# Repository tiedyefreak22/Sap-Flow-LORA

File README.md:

# packet-forwarder

This firmware project was created using [Particle Developer Tools](https://www.particle.io/developer-tools/) and is compatible with all [Particle Devices](https://www.particle.io/devices/).

Feel free to replace this README.md file with your own content, or keep it for reference.

## Table of Contents
- [Introduction](#introduction)
- [Prerequisites To Use This Template](#prerequisites-to-use-this-repository)
- [Getting Started](#getting-started)
- [Particle Firmware At A Glance](#particle-firmware-at-a-glance)
  - [Logging](#logging)
  - [Setup and Loop](#setup-and-loop)
  - [Delays and Timing](#delays-and-timing)
  - [Testing and Debugging](#testing-and-debugging)
  - [GitHub Actions (CI/CD)](#github-actions-cicd)
  - [OTA](#ota)
- [Support and Feedback](#support-and-feedback)
- [Version](#version)

## Introduction

For an in-depth understanding of this project template, please refer to our [documentation](https://docs.particle.io/firmware/best-practices/firmware-template/).

## Prerequisites To Use This Repository

To use this software/firmware on a device, you'll need:

- A [Particle Device](https://www.particle.io/devices/).
- Windows/Mac/Linux for building the software and flashing it to a device.
- [Particle Development Tools](https://docs.particle.io/getting-started/developer-tools/developer-tools/) installed and set up on your computer.
- Optionally, a nice cup of tea (and perhaps a biscuit).

## Getting Started

1. While not essential, we recommend running the [device setup process](https://setup.particle.io/) on your Particle device first. This ensures your device's firmware is up-to-date and you have a solid baseline to start from.

2. If you haven't already, open this project in Visual Studio Code (File -> Open Folder). Then [compile and flash](https://docs.particle.io/getting-started/developer-tools/workbench/#cloud-build-and-flash) your device. Ensure your device's USB port is connected to your computer.

3. Verify the device's operation by monitoring its logging output:
    - In Visual Studio Code with the Particle Plugin, open the [command palette](https://docs.particle.io/getting-started/developer-tools/workbench/#particle-commands) and choose "Particle: Serial Monitor".
    - Or, using the Particle CLI, execute:
    ```
    particle serial monitor --follow
    ```

4. Uncomment the code at the bottom of the cpp file in your src directory to publish to the Particle Cloud! Login to console.particle.io to view your devices events in real time.

5. Customize this project! For firmware details, see [Particle firmware](https://docs.particle.io/reference/device-os/api/introduction/getting-started/). For information on the project's directory structure, visit [this link](https://docs.particle.io/firmware/best-practices/firmware-template/#project-overview).

## Particle Firmware At A Glance

### Logging

The firmware includes a [logging library](https://docs.particle.io/reference/device-os/api/logging/logger-class/). You can display messages at different levels and filter them:

```
Log.trace("This is trace message");
Log.info("This is info message");
Log.warn("This is warn message");
Log.error("This is error message");
```

### Setup and Loop

Particle projects originate from the Wiring/Processing framework, which is based on C++. Typically, one-time setup functions are placed in `setup()`, and the main application runs from the `loop()` function.

For advanced scenarios, explore our [threading support](https://docs.particle.io/firmware/software-design/threading-explainer/).

### Delays and Timing

By default, the setup() and loop() functions are blocking whilst they run, meaning that if you put in a delay, your entire application will wait for that delay to finish before anything else can run. 

For techniques that allow you to run multiple tasks in parallel without creating threads, checkout the code example [here](https://docs.particle.io/firmware/best-practices/firmware-template/).

(Note: Although using `delay()` isn't recommended for best practices, it's acceptable for testing.)

### Testing and Debugging

For firmware testing and debugging guidance, check [this documentation](https://docs.particle.io/troubleshooting/guides/build-tools-troubleshooting/debugging-firmware-builds/).

### GitHub Actions (CI/CD)

This project provides a YAML file for GitHub, automating firmware compilation whenever changes are pushed. More details on [Particle GitHub Actions](https://docs.particle.io/firmware/best-practices/github-actions/) are available.

### OTA

To learn how to utilize Particle's OTA service for device updates, consult [this documentation](https://docs.particle.io/getting-started/cloud/ota-updates/).

Test OTA with the 'Particle: Cloud Flash' command in Visual Studio Code or the CLI command 'particle flash'!

This firmware supports binary assets in OTA packages, allowing the inclusion of audio, images, configurations, and external microcontroller firmware. More details are [here](https://docs.particle.io/reference/device-os/api/asset-ota/asset-ota/).

## Support and Feedback

For support or feedback on this template or any Particle products, please join our [community](https://community.particle.io)!

## Version

Template version 1.0.2

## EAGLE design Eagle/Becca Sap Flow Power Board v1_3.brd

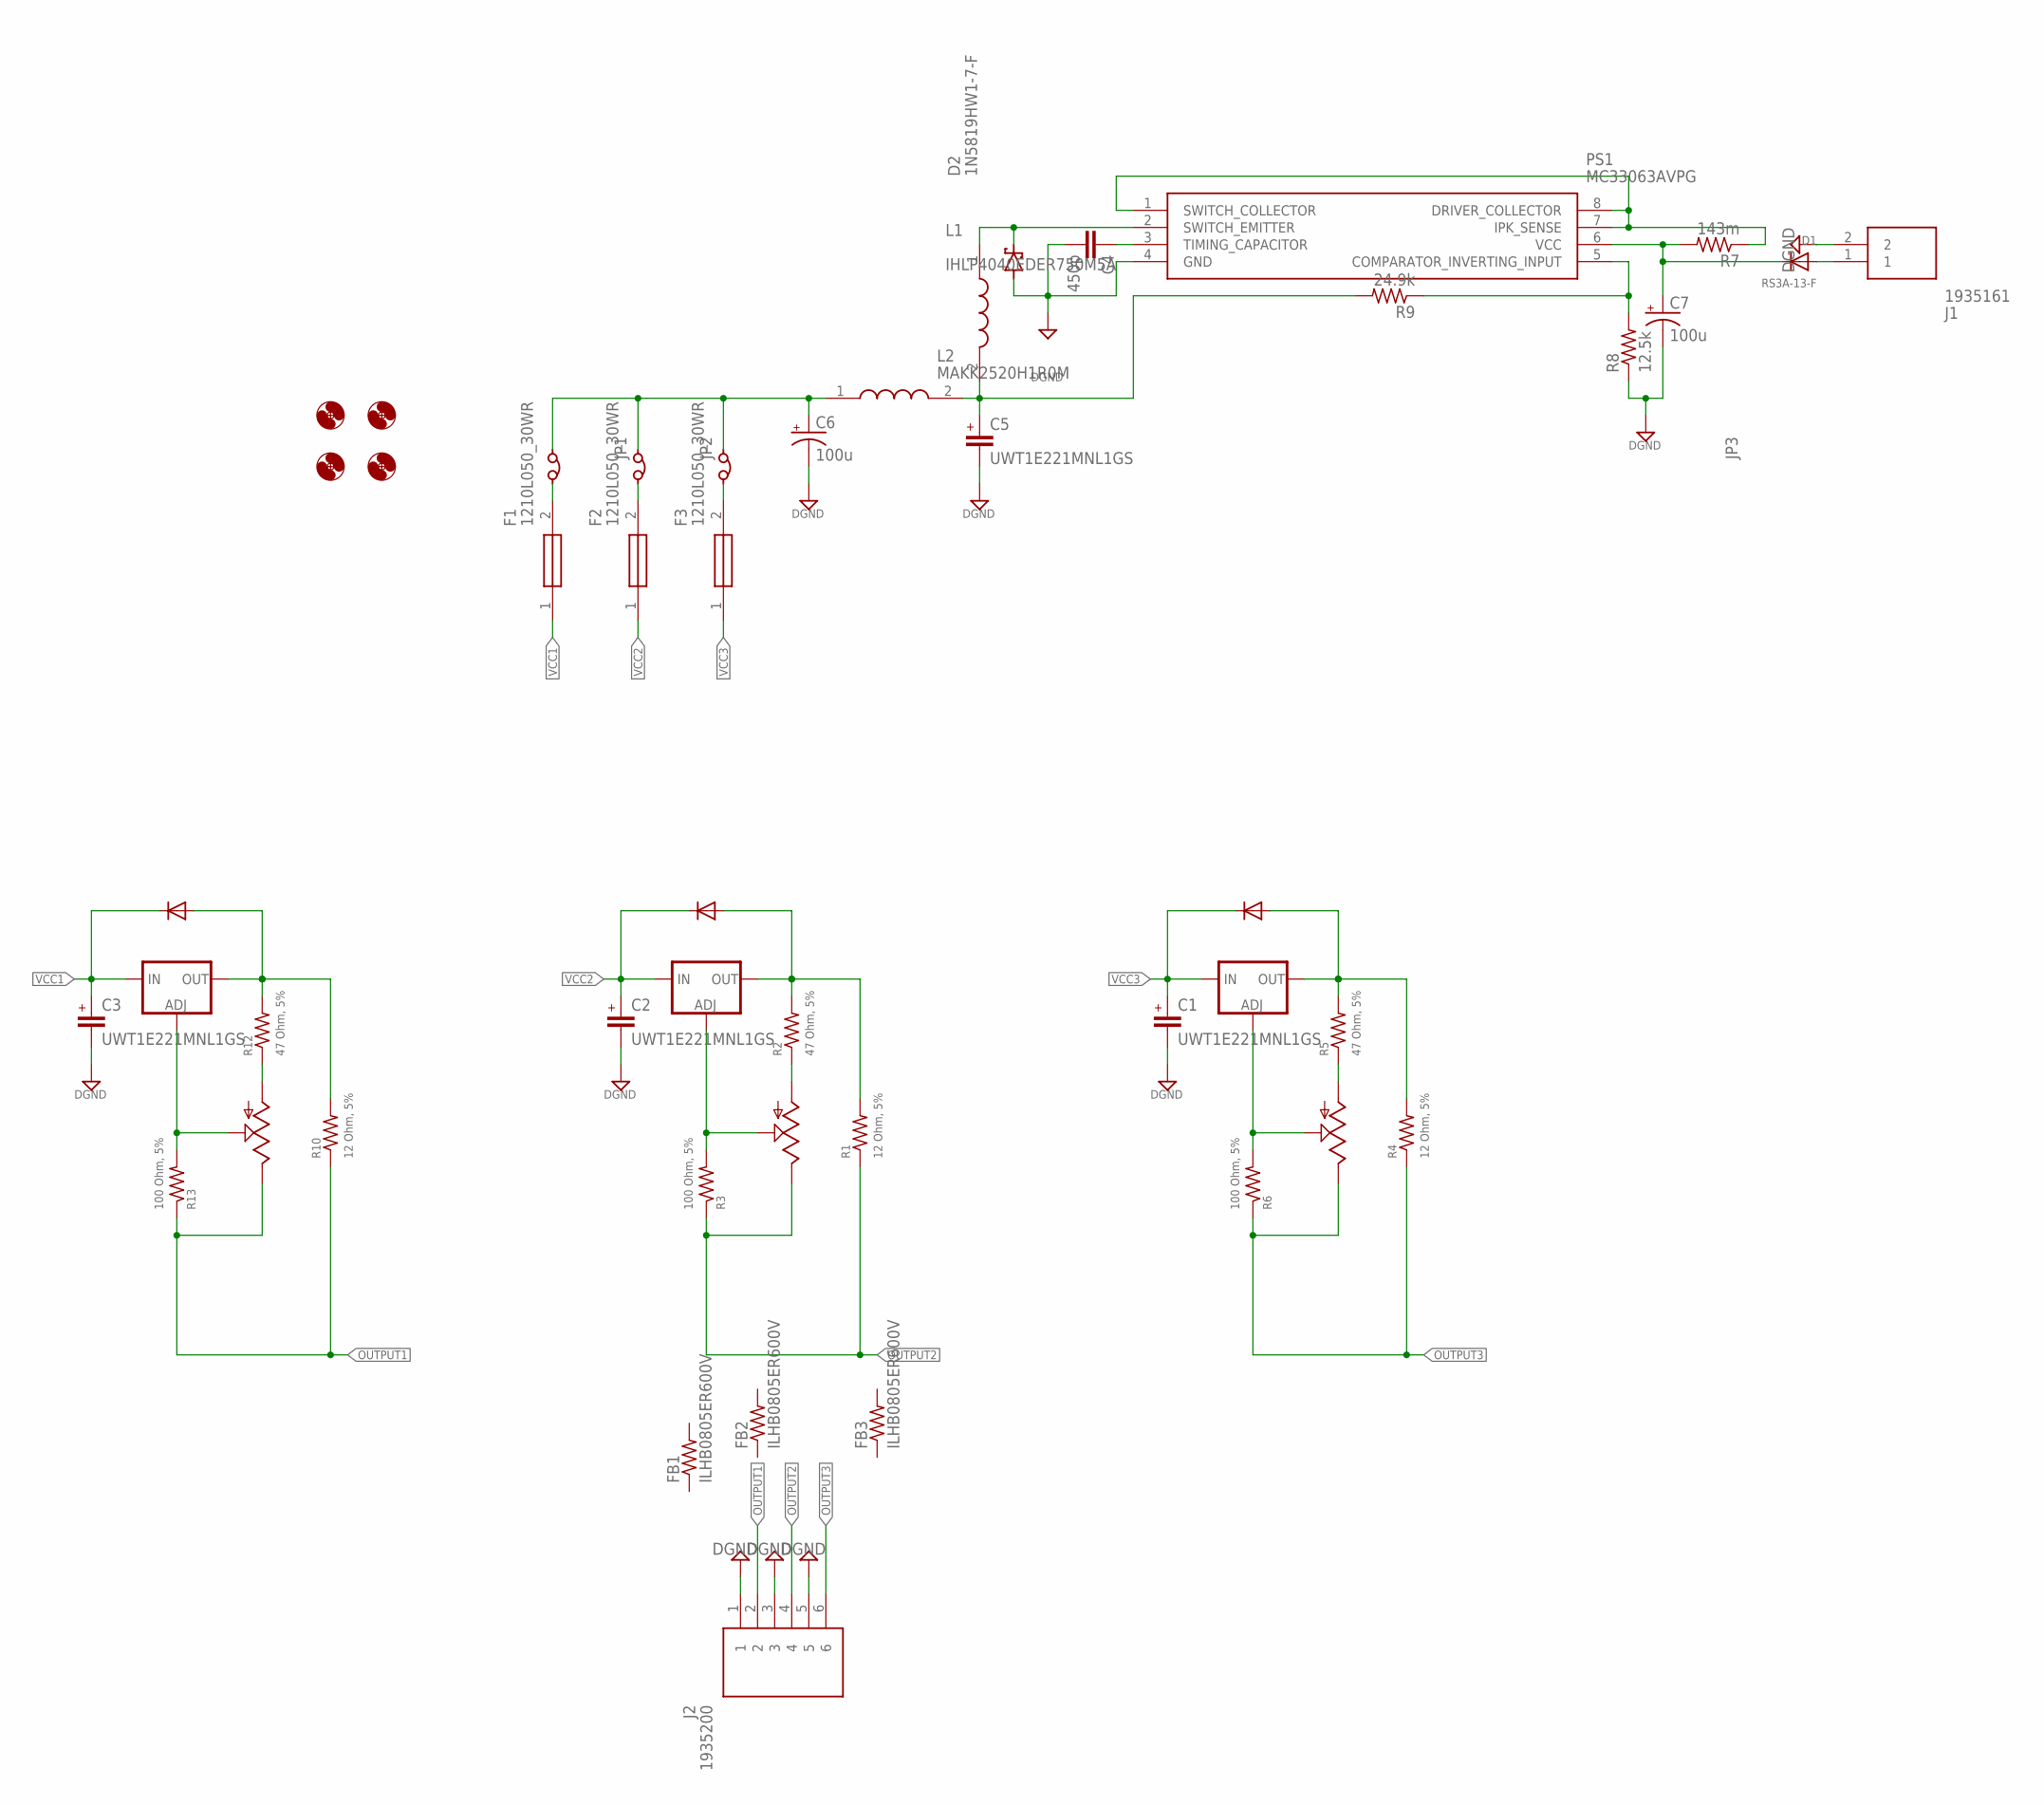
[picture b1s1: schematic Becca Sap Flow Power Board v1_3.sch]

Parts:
C1, C2, C3, C5: UWT1E221MNL1GS; CAPAE830X1080N
C4: 450p; C0603
C6, C7: 100u; E2,5-6
D1: RS3A-13-F; DIOM7959X250N
D2: 1N5819HW1-7-F; SODFL3518X115N
D3, D4, D6: S1A; DIOM5027X250N
F1, F2, F3: 1210L050_30WR; THRMC3226X125N
FB1, FB2, FB3: ILHB0805ER600V; BEADC2012X110N
J1: 1935161
J2: 1935200
JP1, JP2, JP3: JUMPER; HDR2X1
L1: IHLP4040EDER750M5A; INDPM115103X540N
L2: MAKK2520H1R0M
PS1: MC33063AVPG; DIP794W56P254L959H533Q8N
R1, R4, R10: 12 Ohm, 5%; R1210
R2, R5, R12: 47 Ohm, 5%; R1210
R3, R6, R13: 100 Ohm, 5%; R1210
R7: 143m; R0603
R8: 12.5k; R0603
R9: 24.9k; R0603
U1, U2, U3: LM317MBSTT3G; SOT230P700X175-4N
U$1, U$2, U$3, U$4: MOUNT-HOLE3.0; 3,0
VR1, VR2, VR3: 3296W-1-102RLF; 3296W1102RLF

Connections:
DGND: C1.2, C2.2, C3.2, C4.2, C5.2, C6.-, C7.-, D2.2 (A), J1.2, J2.1, J2.3, J2.5, PS1.4 (GND), R8.1
unnamed: C6.+, JP1.1, JP2.1, JP3.1, L2.1
unnamed: D3.2 (A), R1.2, R2.2, U2.2 (OUT)
unnamed: F1.2, JP3.2
unnamed: F2.2, JP1.2
unnamed: D1.2 (A), J1.1
unnamed: PS1.1 (SWITCH_COLLECTOR), PS1.7 (IPK_SENSE), PS1.8 (DRIVER_COLLECTOR), R7.1
unnamed: R3.2, U2.1 (ADJ), VR2.2 (S)
unnamed: F3.2, JP2.2
unnamed: C7.+, D1.1 (K), PS1.6 (VCC), R7.2
unnamed: R2.1, VR2.1 (A)
unnamed: D4.2 (A), R4.2, R5.2, U3.2 (OUT)
unnamed: D6.2 (A), R10.2, R12.2, U1.2 (OUT)
unnamed: R6.2, U3.1 (ADJ), VR3.2 (S)
unnamed: R13.2, U1.1 (ADJ), VR1.2 (S)
unnamed: R12.1, VR1.1 (A)
unnamed: R5.1, VR3.1 (A)
unnamed: C4.1, PS1.3 (TIMING_CAPACITOR)
unnamed: PS1.5 (COMPARATOR_INVERTING_INPUT), R8.2, R9.1
unnamed: D2.1 (C), L1.1, PS1.2 (SWITCH_EMITTER)
unnamed: C5.1, L1.2, L2.2, R9.2
OUTPUT1: J2.2, R10.1, R13.1, VR1.3 (E)
OUTPUT2: J2.4, R1.1, R3.1, VR2.3 (E)
OUTPUT3: J2.6, R4.1, R6.1, VR3.3 (E)
VCC1: C3.1, D6.1 (K), F1.1, U1.3 (IN)
VCC2: C2.1, D3.1 (K), F2.1, U2.3 (IN)
VCC3: C1.1, D4.1 (K), F3.1, U3.3 (IN)

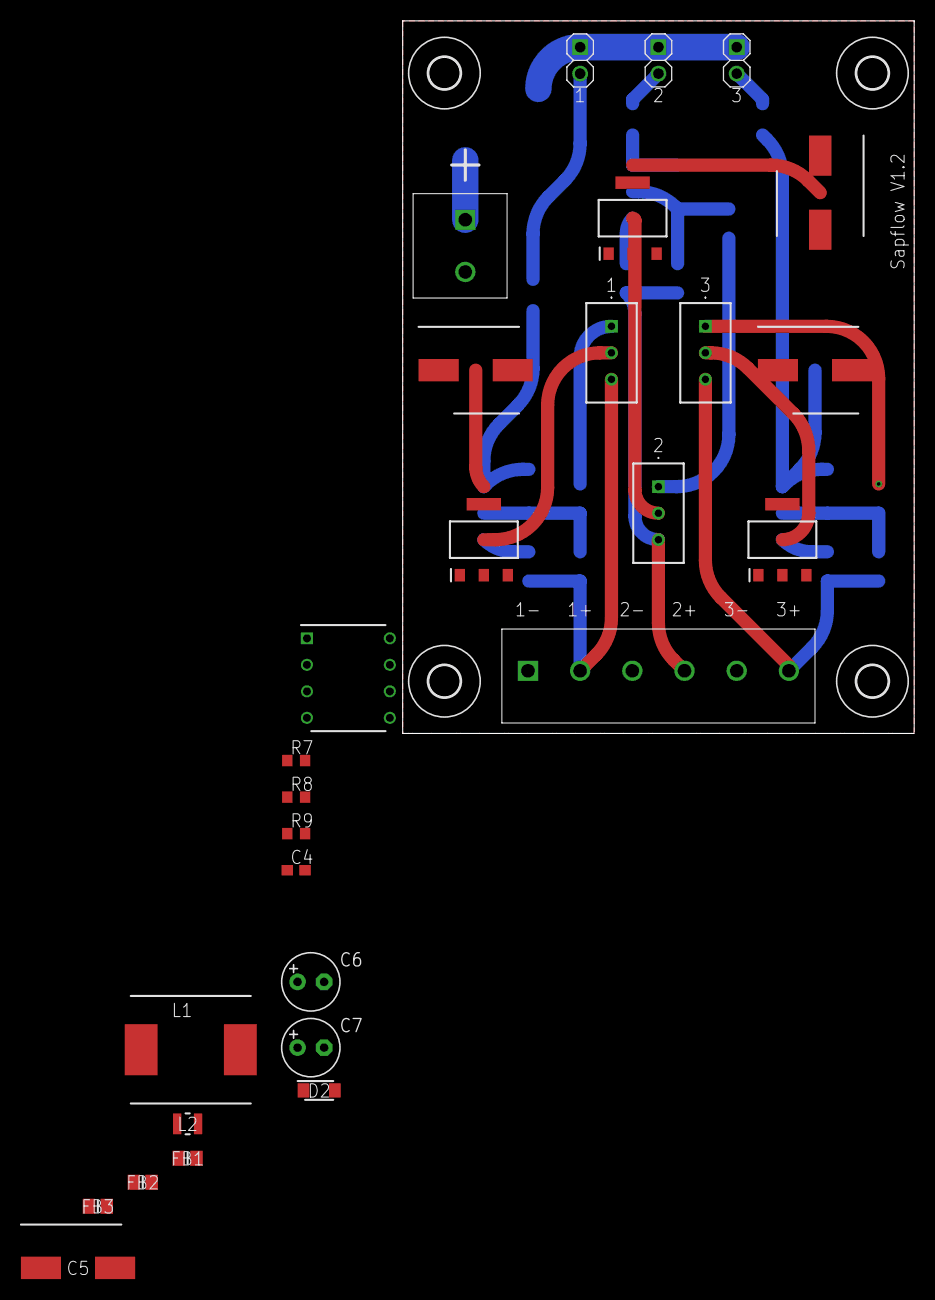
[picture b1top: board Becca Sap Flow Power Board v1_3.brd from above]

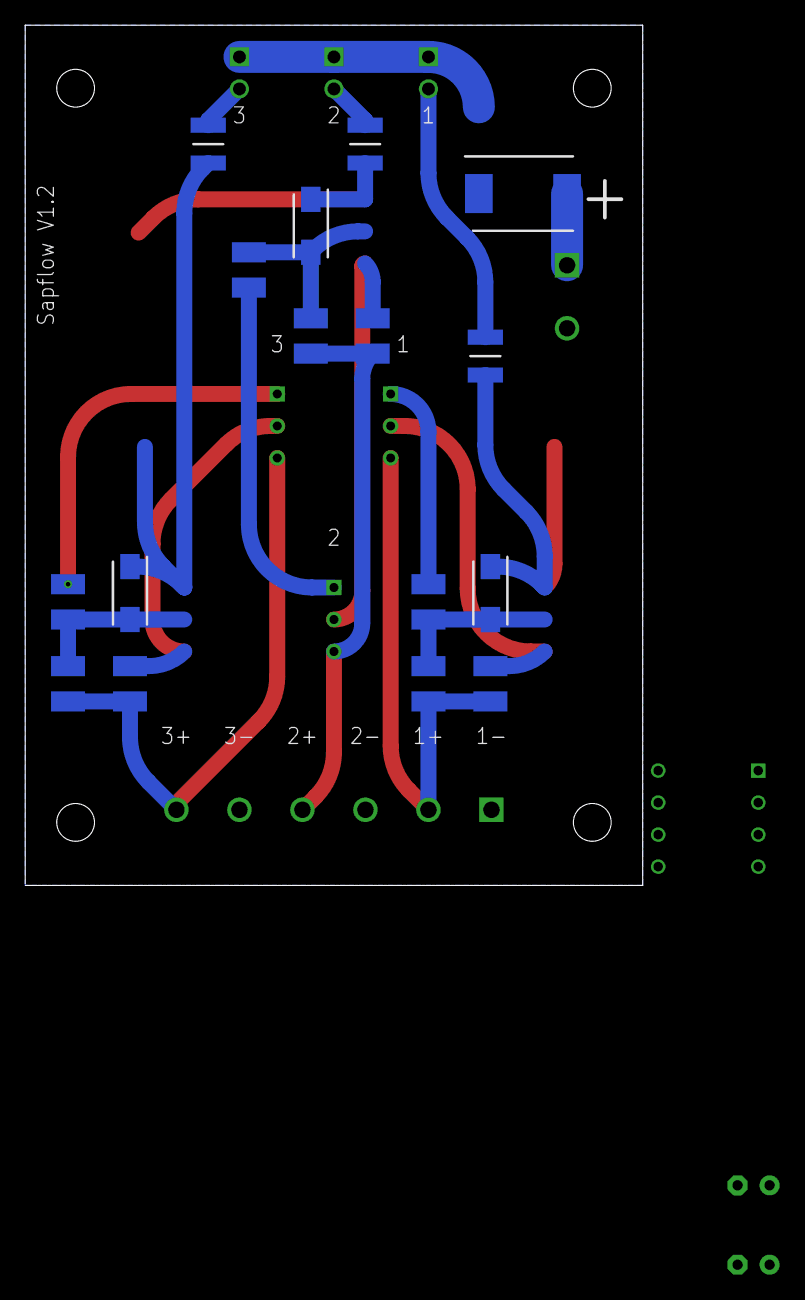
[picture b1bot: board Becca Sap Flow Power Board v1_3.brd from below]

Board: 2 copper layers, 49.0 x 68.3 mm, 48 parts (16 on the bottom side), 27 nets.

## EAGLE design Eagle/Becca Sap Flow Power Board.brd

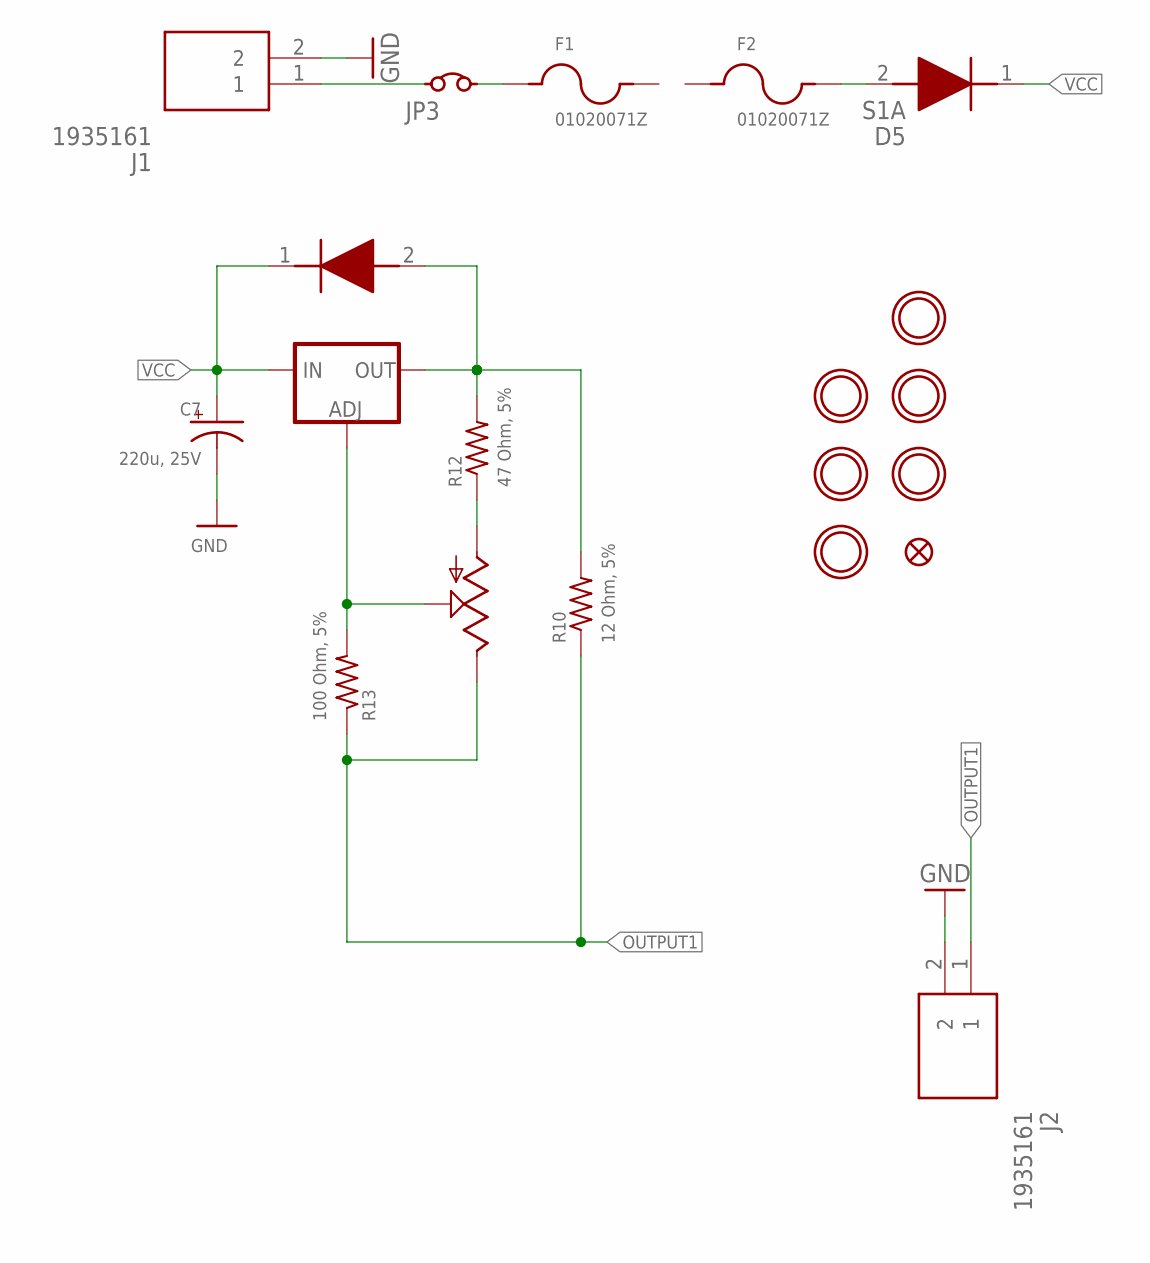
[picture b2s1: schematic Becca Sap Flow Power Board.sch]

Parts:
C7: 220u, 25V; PANASONIC_C
D5, D6: S1A; DIOM5027X250N
F1, F2: 01020071Z
FID2: FIDUCIAL_1MM
J1, J2: 1935161
JP3: JUMPER; HDR2X1
R10: 12 Ohm, 5%; R0805
R12: 47 Ohm, 5%; R0805
R13: 100 Ohm, 5%; R0805
U1: V_REG_317SMD; SOT223
U$1, U$2, U$3, U$4, U$5, U$11: MOUNTINGHOLE2.5; MOUNTINGHOLE_2.5_PLATED
VR1: 3296W-1-102RLF; 3296W1102RLF

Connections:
GND: C7.-, J1.2, J2.2
unnamed: J1.1, JP3.1
unnamed: F1.1, JP3.2
unnamed: D5.2 (A), F2.2
unnamed: D6.2 (A), R10.2, R12.2, U1.2 (OUT)
unnamed: R13.2, U1.1 (ADJ), VR1.2 (S)
unnamed: R12.1, VR1.1 (A)
OUTPUT1: J2.1, R10.1, R13.1, VR1.3 (E)
VCC: C7.+, D5.1 (K), D6.1 (K), U1.3 (IN)

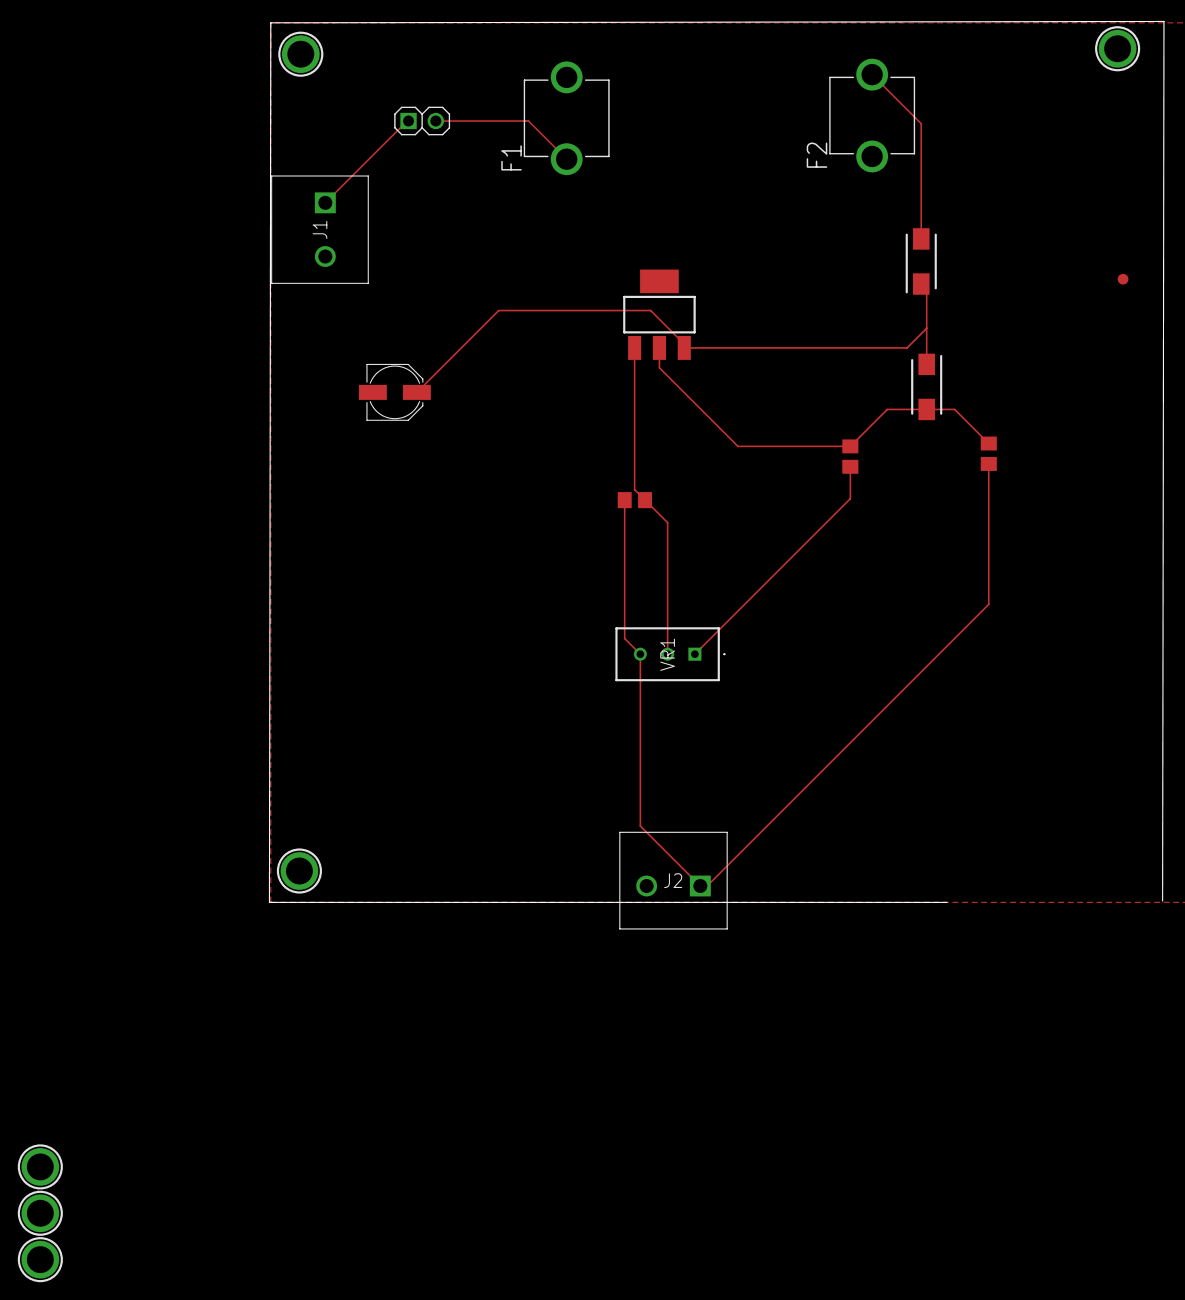
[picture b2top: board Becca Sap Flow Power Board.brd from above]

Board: 2 copper layers, 83.3 x 82.0 mm, 20 parts (0 on the bottom side), 9 nets.

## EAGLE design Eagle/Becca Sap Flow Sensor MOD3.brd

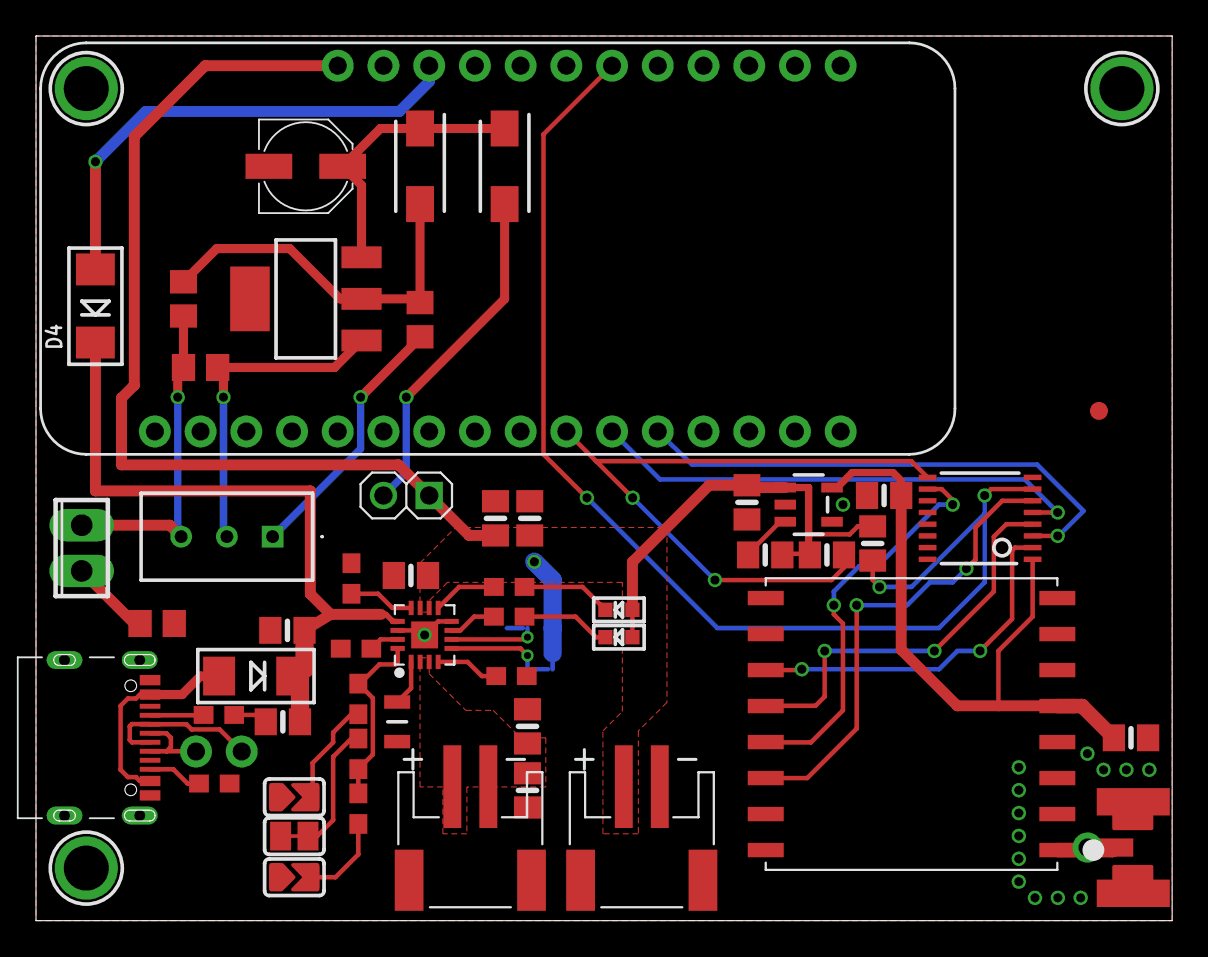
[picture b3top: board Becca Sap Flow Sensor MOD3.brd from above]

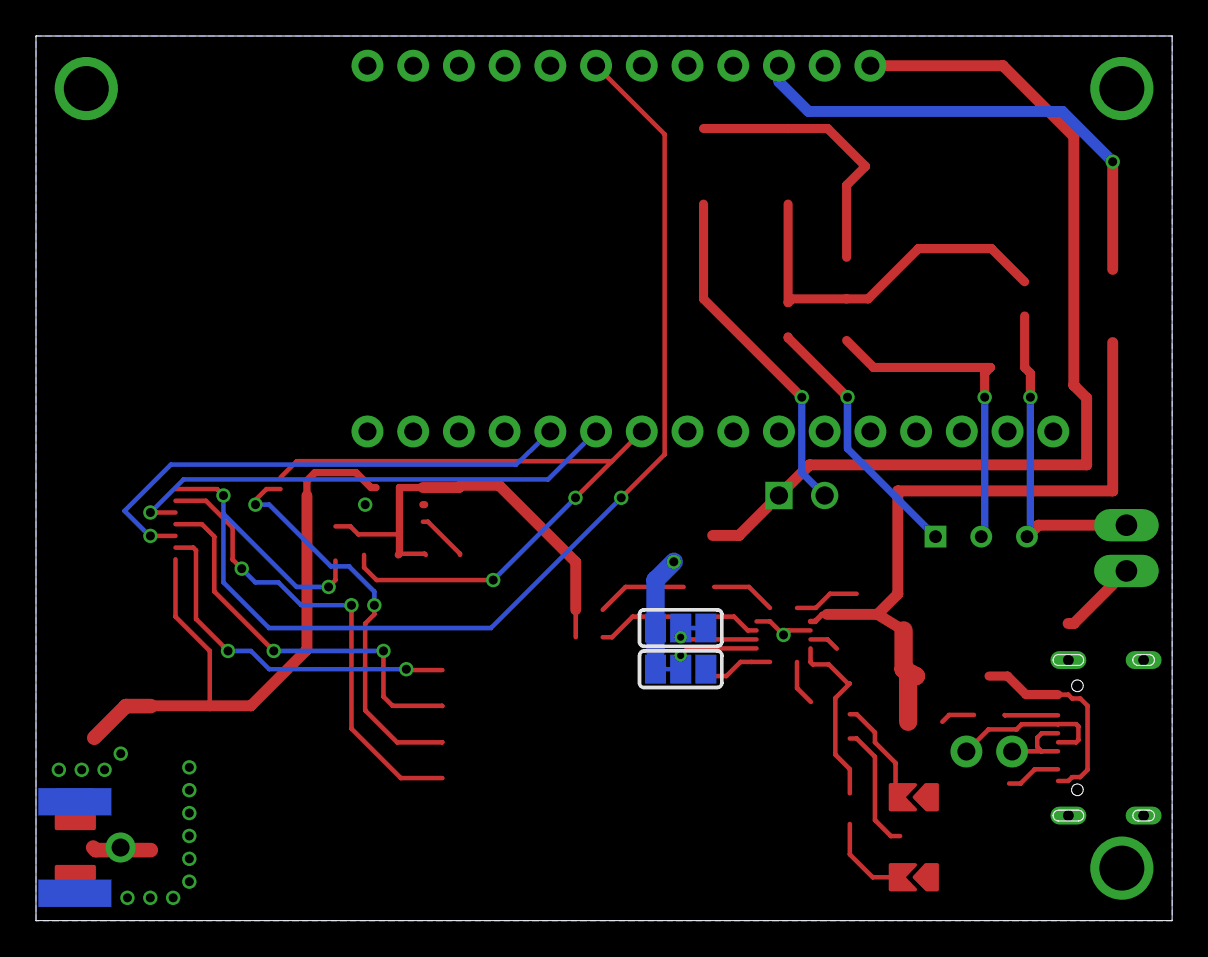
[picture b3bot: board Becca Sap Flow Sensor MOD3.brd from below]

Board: 2 copper layers, 63.1 x 49.1 mm, 59 parts (2 on the bottom side), 42 nets.

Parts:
0.5A, 1.5A: SOLDERJUMPER_ARROW_NOPASTE
1A: SOLDERJUMPER_CLOSEDWIRE
BATT: JST 2PH; JST-PH-2-SMT-RA
C1, C2, C3, C4, C5, C6, C9, C10, C14: 10uF; 0805-NO
C7: 220u, 25V; PANASONIC_C
C8: 0.1uF; 0805-NO
D1: GREEN; CHIPLED_0603
D2, D4: SK34A; SMADIODE
D3: RED; CHIPLED_0603
D5, D6: S1A; DIOM5027X250N
FID2: FIDUCIAL_1MM
JP1: 1X02_ROUND
JP3: JUMPER; HDR2X1
JP7: 1X01_ROUND
R1, R9: 1K; 0603-NO
R2, R7, R8, R11: 10K; 0603-NO
R3: 590; 0603-NO
R4, R6: 5.1K; 0603-NO
R5: 2K; 0603-NO
R10: 12 Ohm, 5%; R0805
R12: 47 Ohm, 5%; R0805
R13: 100 Ohm, 5%; R0805
R14: R of 2 Thermos; R0805
R15, R16, R17: 100K; 0805-NO
RT1: NTCS0805E3103FHT; THRMC2012X95N
SJ1, SJ2: SOLDERJUMPER_2WAY_OPEN_NOPASTE
SYSOUT: JST 2PH; JST-PH-2-SMT-RA
U1: V_REG_317SMD; SOT223
U2: BORON
U6: RFM69HCW; RFMHCW_SMT
U7: 74HC4050D; TSSOP16
U8: AP2112K-3.3; SOT23-5
U$3, U$4, U$11: MOUNTINGHOLE2.5; MOUNTINGHOLE_2.5_PLATED
VR1: 3296W-1-102RLF; 3296W1102RLF
X1: 2POL254
X2: USB Type C; USB_C_CUSB31-CFM2AX-01-X
X4: BQ24074; QFN16_3MM
X5: uFL/SMA; SMA_EDGELAUNCH_UFL

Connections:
3.3V: C8.1, C14.1, U6.5P, U7.1, U8.5
!CE: R8.1, X4.4
!CHG: R7.1, X4.9
!PGOOD: R11.1, X4.7
CC1: R6.2, X2.A5
CC2: R4.2, X2.B5
CS_3V1: U6.13P, U7.10
CS_5V1: R16.1, U2.10, U7.9
D+: JP1.1, X2.A6, X2.B6
D-: JP1.2, X2.A7, X2.B7
EN1: SJ2.2, X4.6
EN2: SJ1.2, X4.5
EN3: R15.2, U8.3
GND: 0.5A.1, 1.5A.1, 1A.1, BATT.2, C1.2, C2.2, C3.2, C4.2, C5.2, C6.2, C7.-, C8.2, C9.2, C10.2, C14.2, R1.2, R2.2, R4.1, R6.1, R8.2, R14.1, RT1.2, SJ1.3, SJ2.3, SYSOUT.2, U2.4, U6.2P, U6.9P, U6.16P, U7.8, U8.2, X2.A1B12, X2.B1A12, X4.8, X4.14, X4.THERMAL, X5.GND@1, X5.GND@2, X5.GND@3, X5.GND@4
ILIM: R1.1, X4.12
ISET: R3.1, R5.1, R9.1, X4.16
ITERM: R2.1, X4.15
MOSI_3V1: U6.11P, U7.2
MOSI_5V1: U2.12, U7.3
unnamed: D1.C, R11.2
unnamed: D3.C, R7.2
unnamed: 1.5A.2, R3.2
unnamed: 0.5A.2, R5.2
unnamed: 1A.2, R9.2
unnamed: RT1.1, X4.1
unnamed: D5.2, JP3.2
unnamed: C7.+, D5.1, D6.1, U1.3
unnamed: D6.2, R10.2, R12.2, U1.2
unnamed: R14.2, X1.1
unnamed: R13.2, U1.1, VR1.2
unnamed: R12.1, VR1.1
unnamed: R10.1, R13.1, VR1.3, X1.2
unnamed: JP7.1, U6.1P, X5.P
OUT: C2.1, C3.1, C4.1, C10.1, D1.A, D3.A, JP3.1, R15.1, R16.2, R17.2, SJ1.1, SJ2.1, SYSOUT.1, U2.28, U8.1, X4.10, X4.11
RST_3V1: U6.14P, U7.6
RST_5V1: R17.1, U2.22, U7.7
SCK_3V1: U6.12P, U7.4
SCK_5V1: U2.11, U7.5
VBUS: C1.1, C9.1, D2.C, D4.C, X4.13
VLIPO: BATT.1, C5.1, C6.1, X4.2, X4.3
VUSB: D2.A, X2.A4B9, X2.B4A9
VUSB1: D4.A, U2.26

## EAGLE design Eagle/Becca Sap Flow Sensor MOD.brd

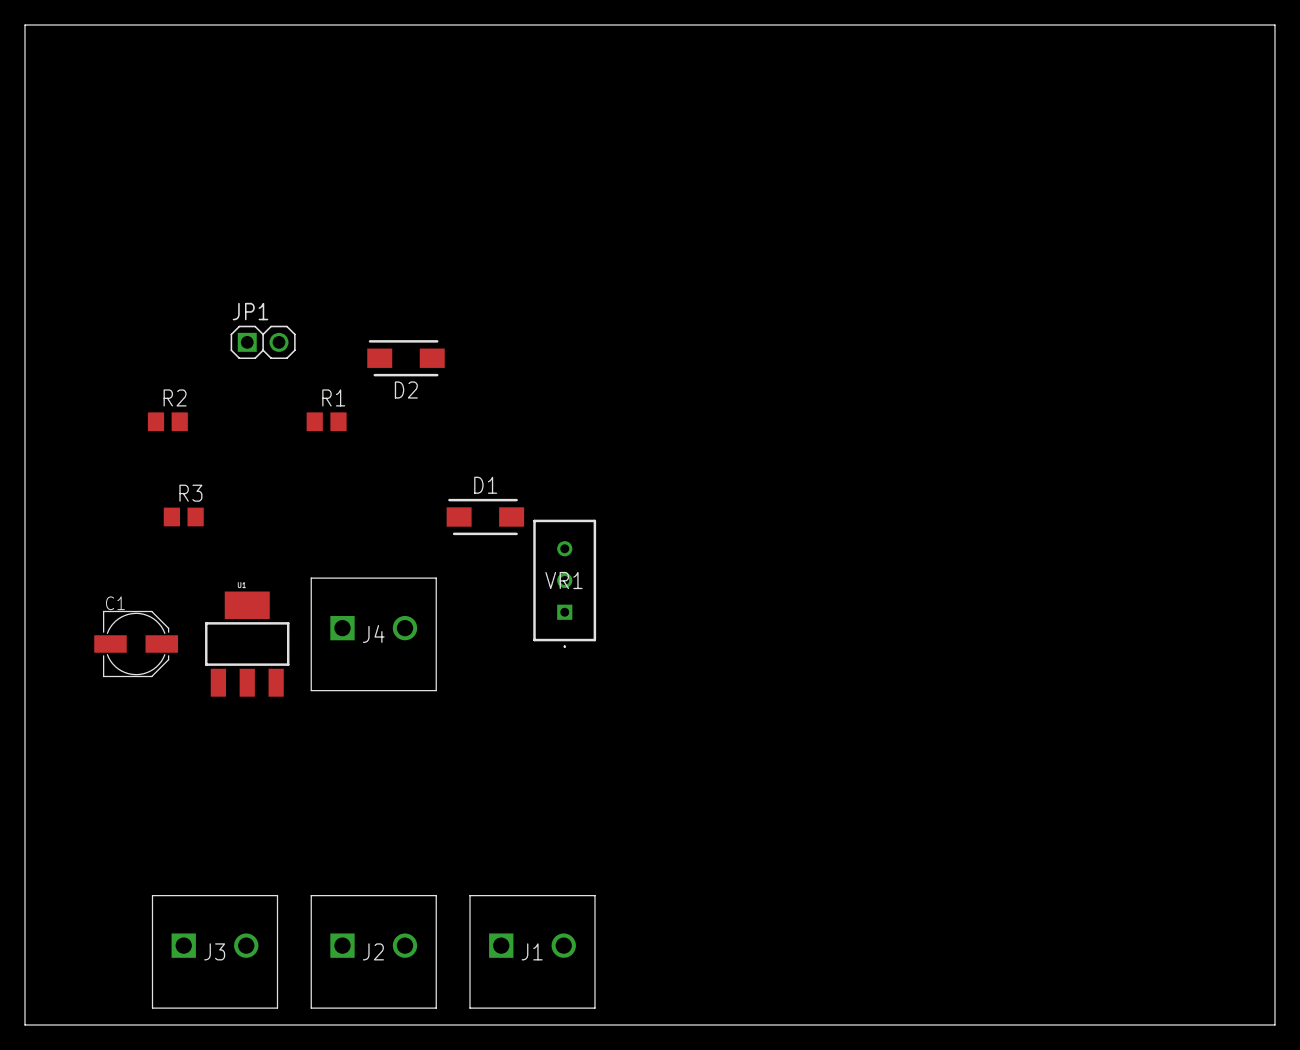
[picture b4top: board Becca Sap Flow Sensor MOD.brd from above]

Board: 2 copper layers, 100.0 x 80.0 mm, 13 parts (0 on the bottom side), 10 nets, no tracks yet.

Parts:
C1: 220u, 25V; PANASONIC_C
D1, D2: S1A; DIOM5027X250N
J1, J2, J3, J4: 1935161
JP1: JUMPER; HDR2X1
R1: 12 Ohm, 5%; R0805
R2: 47 Ohm, 5%; R0805
R3: 100 Ohm, 5%; R0805
U1: V_REG_317SMD; SOT223
VR1: 3296W-1-102RLF; 3296W1102RLF

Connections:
GND: C1.-, J3.1, J4.2
unnamed: D1.2, JP1.2
unnamed: C1.+, D1.1, D2.1, U1.3
unnamed: D2.2, R1.2, R2.2, U1.2
unnamed: J2.1, J3.2
unnamed: J1.1, J2.2
unnamed: R3.2, U1.1, VR1.2
unnamed: R2.1, VR1.1
unnamed: J1.2, R1.1, R3.1, VR1.3
VCC: J4.1, JP1.1

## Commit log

2024-03-16 combining tx and rx files
2024-03-16 Organized files and added additional (hopefully) working example
2024-03-16 Good progress!
2024-03-17 Adding Eagle files
2024-03-17 Initial Committ
2024-03-31 Got radios working again on new windows
2024-03-31 Initial datagram try
2024-03-31 Got datagram working!
2024-04-01 More Eagle work
2024-04-02 added google sheets integration test
2024-08-15 Implemented datalogging on TX2 file
2024-09-28 Amended git ignore, also adding most recent sch
2024-09-28 Adding Aligntrack stuff
2024-09-28 More Aligntrack script progress and organization
2024-09-29 Beginning to port the lora physical layer into c
2024-09-30 Added time constraints and attempts limitations
2024-09-30 Fixed serial contingency
2024-09-30 Adding bin file of rtl-sdr output
2024-09-30 Changed to a much better structure for the project
2024-10-22 Addded AlignTrack Matlab Scripts
2024-10-23 Added more lora parameters
2024-10-23 Adding more temp lora files
2024-10-23 Successfully decoded LoRa!!!
2024-10-23 LoRaPHY C++ progress
2024-10-25 Progress!
2024-10-25 Moar progress.
    Changed some of the helper functions. Might need to revert. Also needed to accost chatgpt over the demodulate function, so confidence isn't exactly sky high that it's correct.
2024-10-25 Modulation/encoding works but demodulation/decoding does not
2024-10-25 Improvement but the samples variable still isn't long enough for some reason
2024-10-27 More comprehensive LoRa class creation
2024-10-28 Pre-comprehensive translation
2024-10-30 Still not right, but most comprehensive representation in c++ of the LoRaPHY matlab script
2024-10-30 Progress and matlab baseline
2024-11-01 Work on understanding AlignTrack
2024-11-01 Adding original email files and new multiple signal test script
2024-11-10 Added window functions and implementation, reorganized
2024-11-10 Added more windows
2024-11-18 Adding variable outputs image and some formatting changes, also additions
2024-11-19 Progress?
2024-11-19 Final progress before class
2024-11-20 Moar Progress
2024-11-20 Added start correlation. Need to add logic to calculate subsequent packet offset
2024-11-20 Added semi-functional time shift based on fft peaks
2024-11-20 Figured out the necessary array structure
2024-11-20 Added window multiplication function
2024-11-20 Done for today I think
2024-11-26 Finally figured out how aligntrack works
2024-11-26 adding only unique messages
2024-11-26 Implemented cross-correlation of outputs with inputs to determine best comparison for BER
2024-11-26 Implemented BER!
2024-11-27 Fixed offset issues
2024-11-27 Done except for cleanup?
2024-11-30 Added savefig commands
2024-11-30 BER to SER and organization
2024-11-30 Split out more functions
2024-12-01 Ran 100 iterations
2024-12-02 Made a lot of progress on presentation
2024-12-03 Finished presentation?
2024-12-05 Adding new script for rtl-sdr reintegration
2024-12-05 Started adding frft stuff, although input parameters to the functions need refining
2024-12-06 Got fractional fourier transform working
2024-12-06 Pre-100 run
2024-12-06 Finished for now
2024-12-08 Changed regular aligntrack script for comparison
2024-12-09 Added line to read out SNR
2025-06-19 Adding power board
2025-06-20 Progress
2025-06-22 Finished boards, generated gerbers and BOM
2025-08-03 Adding V1.1
2025-08-04 Moved files and adding 1.2
2025-08-09 Updated excel spreadsheet and added gerbers for V1.2
2025-08-23 Minor updates
2025-09-21 Next version of board
2025-09-22 Adding switching power supply calculator
2025-09-22 More new board progress
2026-02-16 Adding matlab to python conversion functions
2026-03-07 Started python conversion
2026-03-14 Started work on creating python LoraPHY layer and updated gitignore
2026-03-14 Reorganized
2026-03-22 xcode proj updates
2026-03-22 More Xcode updates
2026-03-22 Some progress

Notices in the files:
parts and their libraries:
SparkFun-IC-Power: Licensing: Creative Commons ShareAlike 4.0 International - https://creativecommons.org/licenses/by-sa/4.0
Particle-Devices: Licensing: Designed by Particle.
